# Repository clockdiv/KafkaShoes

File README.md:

# KafkaShoes
Mechanical Shoes for theatre play "Kafka - Der Prozess" at Theater St. Gallen/Switzerland. Ten pair of these shoes were produced at departement of contemporary puppetry arts at Ernst Busch school for performing arts in Berlin/Germany and animated by puppetry students at named play. 

The electronics, firmware and parts of the hardware can be found here in this repository. It would be difficult to recreate them exactly the same way and is more meant as a learning ressource and inspiration.

## Hardware and electronics

Shoes themselves are made of rubber/latex with a lasered steel base. Two geared motors conrol the movement. LiPo battery is hidden in the right shoe.

The sender works with an ESP32 microcontroller, the shoe itself with an ESP8266. Not using the same microcontroller had historical reasons - they were not meant to be controlled via remote control but over WiFi and we had spare ESP8266. The remote control needed at least two analog inputs which the ESP8266 does not provide, so ESP32 was used.

## Software

Today the ESPs are connected via the ESPNOW protocol. First versions were using UDP/IP with OSC Messages.

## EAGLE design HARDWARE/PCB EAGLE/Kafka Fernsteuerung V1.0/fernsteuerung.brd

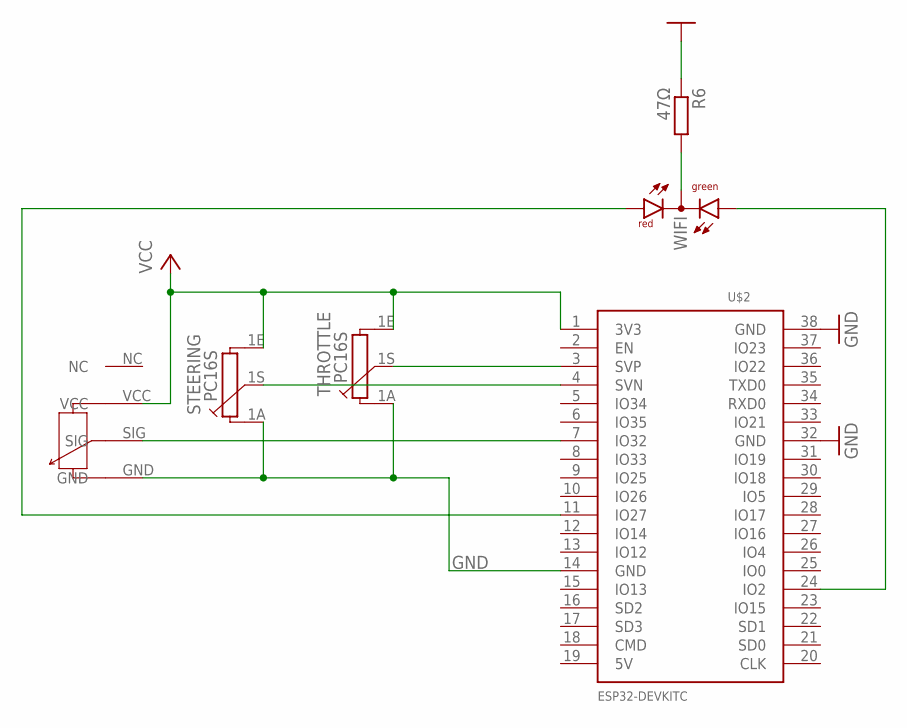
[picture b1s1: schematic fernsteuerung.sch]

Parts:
R6: 47Ω; R0603
STEERING: PC16S
THROTTLE: PC16S
TRIM: ALPS_RK11K
U$2: ESP32DEVKITC; ESP32-DEVKITC
WIFI: DUOLED-RG-C3MM; DUOLED-A-3MM

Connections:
GND: R6.1, STEERING.1A, THROTTLE.1A, TRIM.GND, U$2.14 (GND), U$2.32 (GND), U$2.38 (GND)
unnamed: U$2.11 (IO27), WIFI.3 (AR)
unnamed: TRIM.SIG, U$2.7 (IO32)
unnamed: STEERING.1S, U$2.4 (SVN)
unnamed: THROTTLE.1S, U$2.3 (SVP)
unnamed: R6.2, WIFI.2 (C)
VCC: STEERING.1E, THROTTLE.1E, TRIM.VCC, U$2.1 (3V3)
WIFI_STATUS: U$2.24 (IO2), WIFI.1 (AG)

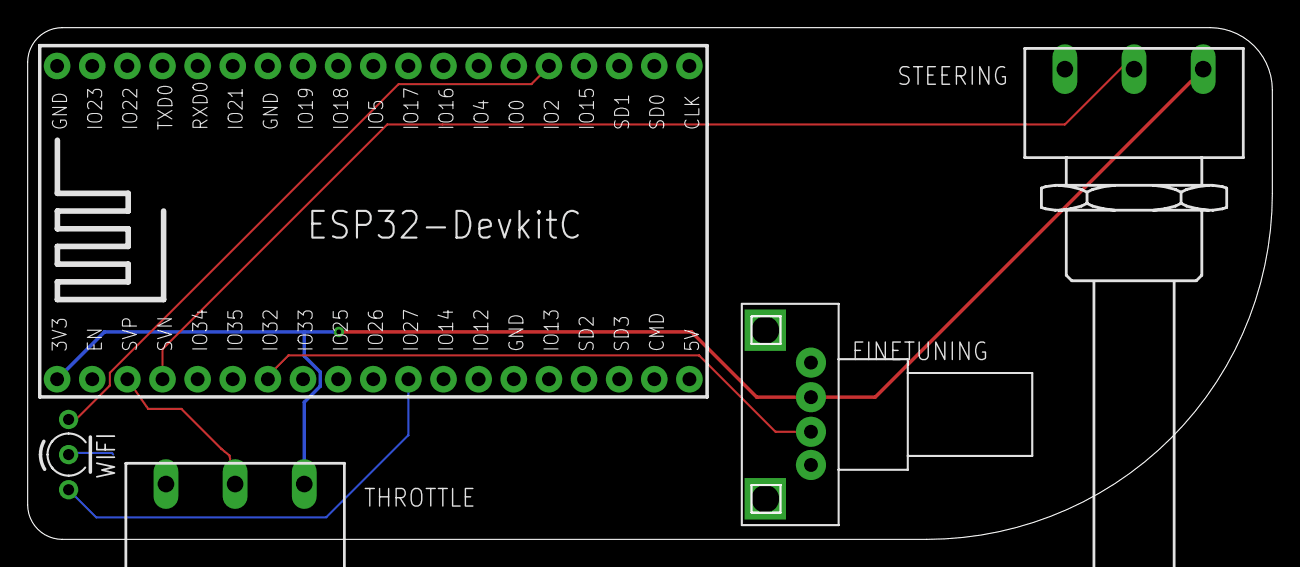
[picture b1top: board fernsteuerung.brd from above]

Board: 2 copper layers, 89.8 x 36.8 mm, 6 parts (1 on the bottom side), 8 nets.

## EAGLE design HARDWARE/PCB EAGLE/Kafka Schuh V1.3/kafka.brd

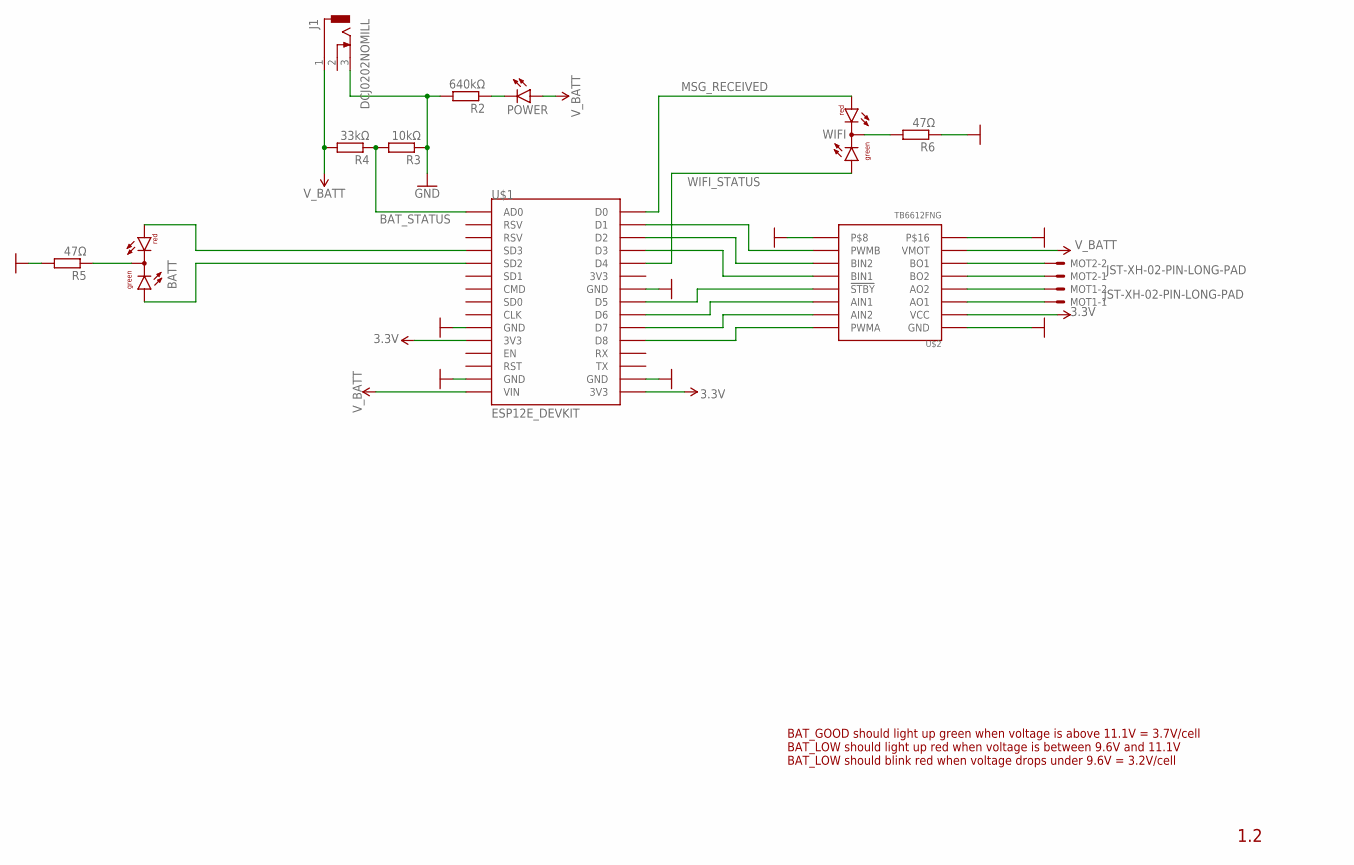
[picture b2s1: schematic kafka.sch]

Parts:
BATT: DUOLED-RG-C3MM; DUOLED-A-3MM
J1: DCJ0202NOMILL; DCJ0202_NOMILL
MOT1, MOT2: JST-XH-02-PIN-LONG-PAD; JST-XH-02-PACKAGE-LONG-PAD
POWER: LED3MM
R2: 640kΩ; R0603
R3: 10kΩ; R0603
R4: 33kΩ; R0603
R5, R6: 47Ω; R0603
U$1: ESP12E_DEVKIT
U$2: TB6612FNG
WIFI: DUOLED-RG-C3MM; DUOLED-A-3MM

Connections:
3.3V: U$1.3V3@2 (3V3), U$2.VCC
AIN1: U$1.D6, U$2.AIN1
AIN2: U$1.D7, U$2.AIN2
BAT_STATUS: R3.2, R4.1, U$1.AD0
BIN1: U$1.D3, U$2.BIN1
BIN2: U$1.D2, U$2.BIN2
GND: J1.3, R2.2, R3.1, R5.2, R6.1, U$1.GND@0 (GND), U$1.GND@1 (GND), U$1.GND@2 (GND), U$1.GND@3 (GND), U$2.GND, U$2.TB6612FNG1, U$2.TB6612FNG2
MSG_RECEIVED: U$1.D0, WIFI.3 (AR)
unnamed: MOT2.2, U$2.BO1
unnamed: MOT2.1, U$2.BO2
unnamed: MOT1.2, U$2.AO2
unnamed: MOT1.1, U$2.AO1
unnamed: R6.2, WIFI.2 (C)
unnamed: POWER.K (C), R2.1
unnamed: BATT.1 (AG), U$1.SD2
unnamed: BATT.3 (AR), U$1.SD3
unnamed: BATT.2 (C), R5.1
PWMA: U$1.D8, U$2.PWMA
PWMB: U$1.D1, U$2.PWMB
STBY: U$1.D5, U$2.!STBY
V_BATT: J1.1, POWER.A, R4.2, U$1.VIN, U$2.VMOT
WIFI_STATUS: U$1.D4, WIFI.1 (AG)

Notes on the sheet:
1.2
BAT_GOOD should light up green when voltage is above 11.1V = 3.7V/cell BAT_LOW should light up red when voltage is between 9.6V and 11.1V BAT_LOW should blink red when voltage drops under 9.6V = 3.2V/cell

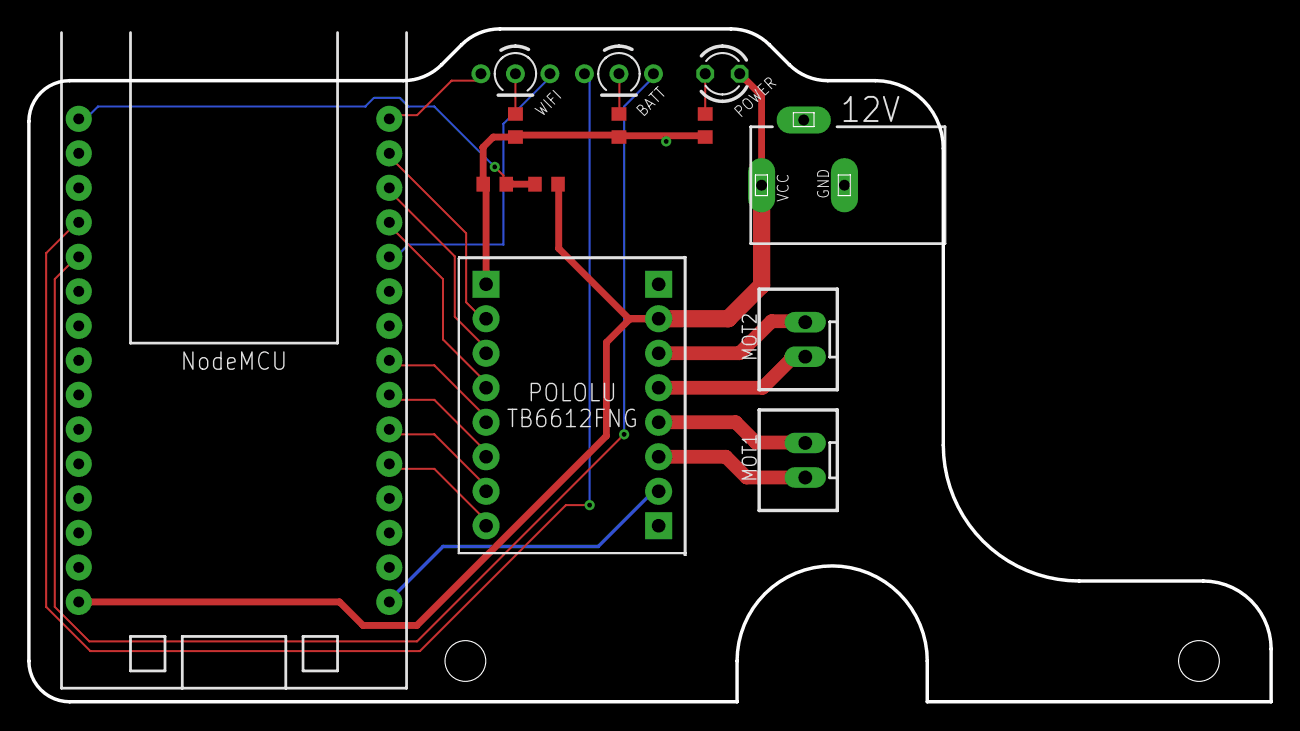
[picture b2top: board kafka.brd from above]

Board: 2 copper layers, 91.4 x 49.5 mm, 13 parts (0 on the bottom side), 22 nets.

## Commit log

2022-01-22 Initial Commit
    initial commit aka backup and finally publishing it
2022-02-23 added all shoes
    added MAC Adresses of many more shoes!

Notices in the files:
parts and their libraries:
SparkFun-PowerSymbols_jj: Licensing: Creative Commons ShareAlike 4.0 International - https://creativecommons.org/licenses/by-sa/4.0
